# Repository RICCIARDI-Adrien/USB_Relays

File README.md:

# USB relays

Control separately 16 signal relays through a PC by using a standard USB connection and a simple text-based serial protocol.  
Each relay can switch up to 3A at 24VDC (warning : this board is not designed for AC current).  
There is no need for a separate power supply to power the board, it is designed to be fully powered by the USB connection (that's why small relays are used).

## Communication protocol

* The board provides an USB serial port with the following settings : **115200 bits/s, no parity, 1 stop bit**.
* All commands are ASCII-only to allow to easily use the board with a simple serial port terminal like `Putty`, `minicom`, `picocom`, etc. If you plan to send commands manually, enable local echo and send CRLF when pressing enter key (see below). Here is an example picocom command invocation : `picocom --echo --omap crcrlf -b 115200 /dev/ttyUSB0`.
* All commands start with the character `#`. This way, if you mess up and write the commands into an UNIX terminal, they will be interpreted as comments.
* All commands end with CRLF characters (`\r\n`), so you only have to press `enter` key to send the command to the board.
* All commands sent to the board return an answer, the board will ignore all other commands while it is processing the current one. This allows to throttle a fast PC sending too much commands at a time, it must wait for each command answer before sending the next one.
* If you don't know the board state (for instance, the PC rebooted while it was sending a command and the board has received an incomplete command and is stuck waiting for the remaining part of the command), send the `!` character at any time. The board will immediately clear its reception buffer.

## Commands list

Use the `#H<CR><LF>` command to display the following list of commands :
```
Commands :
  - Get a relay state : #Gxx
    'xx' is the relay ID, from 1 to 16.
  - Display this help : #H
  - Set led state : #Lv
    'v' is the led state value (0 to turn off, 1 to turn on, 2 to make it blink).
  - Set relay state : #Sxxv
    'xx' is the relay ID, from 1 to 16.
    'v' is the relay state value (0 to clear, 1 to set).
  - Get firmware version : #V
```

## Photo gallery

### Casing plates

Plates are made of 4mm-thick 304 stainless steel.

### PCB

PCB top :

PCB bottom :

### Assembled PCB

Assembled PCB top :

Assembled PCB bottom :

### Casing assembly

Screwing the bolts on the casing lower steel plate :

Fixing the PCB :

Fixing the casing upper steel plate :

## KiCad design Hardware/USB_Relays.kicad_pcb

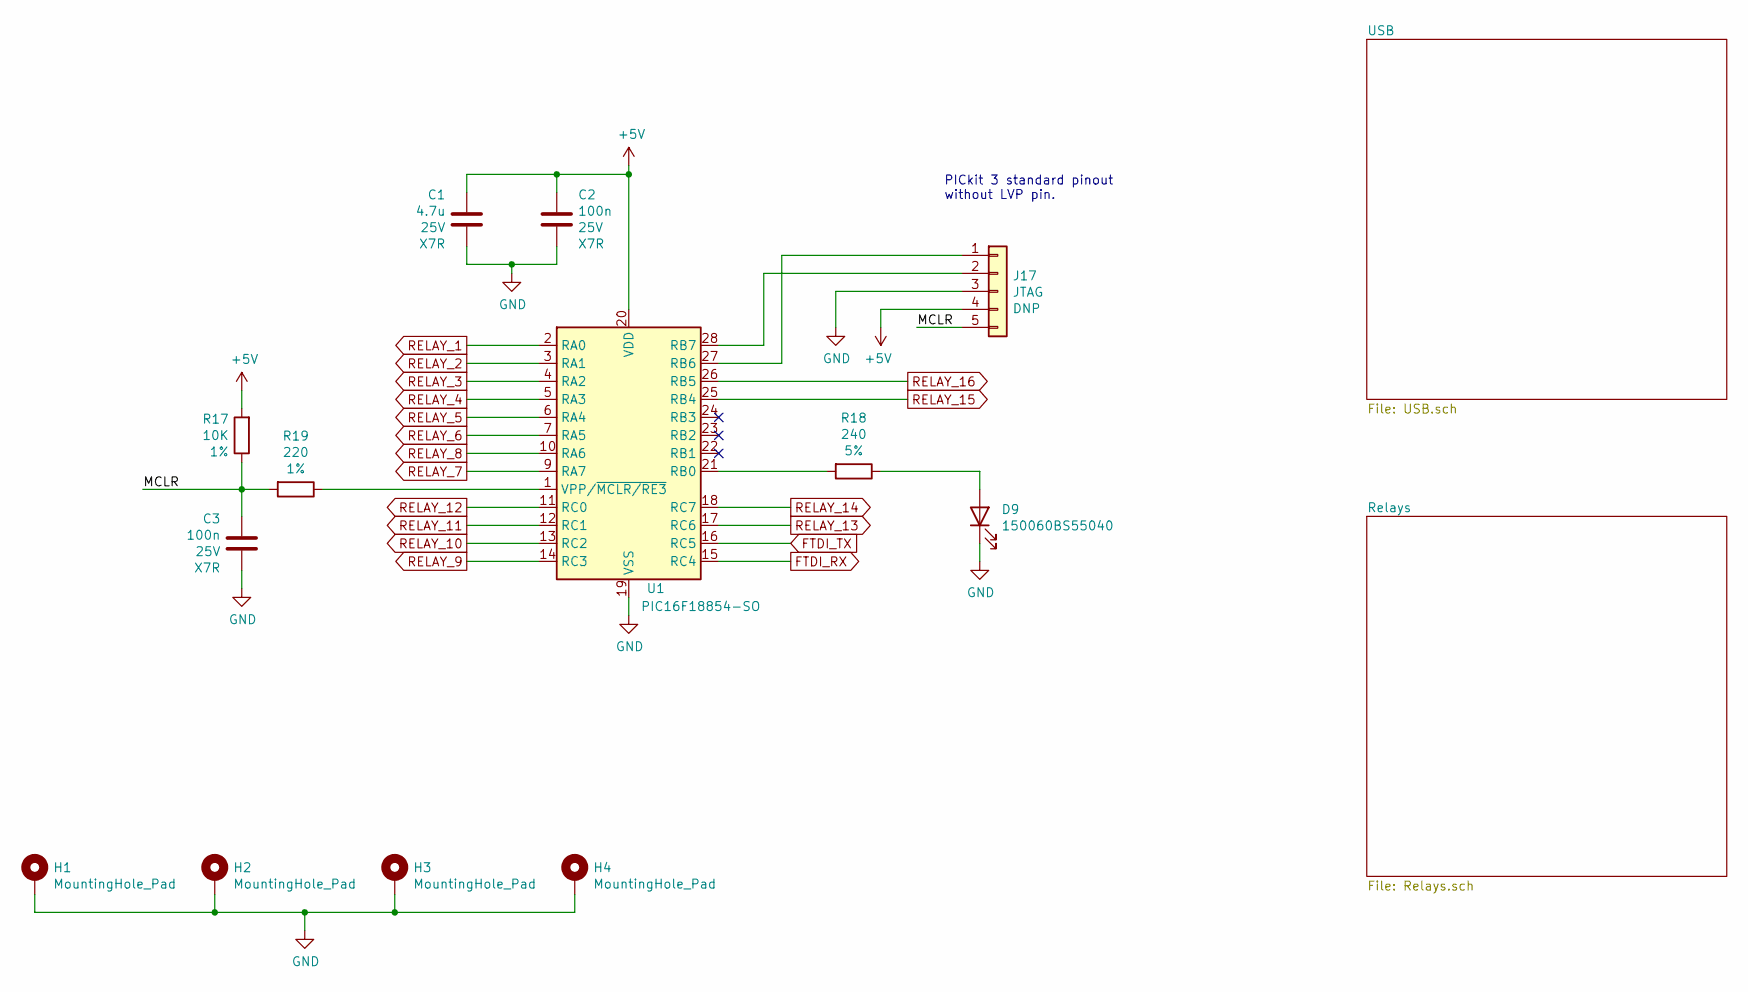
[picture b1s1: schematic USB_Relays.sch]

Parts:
C1: 4.7u; C_0805_2012Metric_Pad1.18x1.45mm_HandSolder
C2, C3: 100n; C_0603_1608Metric_Pad1.08x0.95mm_HandSolder
D9: 150060BS55040; LED_0603_1608Metric_Pad1.05x0.95mm_HandSolder
H1, H2, H3, H4: MountingHole_Pad; MountingHole_4.5mm_Pad
J17: JTAG; PinHeader_1x05_P2.54mm_Vertical
R17: 10K; R_0603_1608Metric_Pad0.98x0.95mm_HandSolder
R18: 240; R_1206_3216Metric_Pad1.30x1.75mm_HandSolder
R19: 220; R_0603_1608Metric_Pad0.98x0.95mm_HandSolder
U1: PIC16F18854-SO; SOIC-28W_7.5x17.9mm_P1.27mm

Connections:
+5V: C1.1, C2.1, J17.4, R17.2, U1.20 (VDD); also elsewhere on the board
/MCLR: C3.1, J17.5, R17.1, R19.2
FTDI_RX: U1.15 (RC4); also elsewhere on the board
FTDI_TX: U1.16 (RC5); also elsewhere on the board
GND: C1.2, C2.2, C3.2, D9.1 (K), H1.1, H2.1, H3.1, H4.1, J17.3, U1.8 (VSS), U1.19 (VSS); also elsewhere on the board
unnamed: D9.2 (A), R18.1
unnamed: J17.1, U1.27 (RB6)
unnamed: J17.2, U1.28 (RB7)
unnamed: R18.2, U1.21 (RB0)
unnamed: R19.1, U1.1 (VPP/~MCLR/RE3)
RELAY_1: U1.2 (RA0); also elsewhere on the board
RELAY_2: U1.3 (RA1); also elsewhere on the board
RELAY_3: U1.4 (RA2); also elsewhere on the board
RELAY_4: U1.5 (RA3); also elsewhere on the board
RELAY_5: U1.6 (RA4); also elsewhere on the board
RELAY_6: U1.7 (RA5); also elsewhere on the board
RELAY_7: U1.9 (RA7); also elsewhere on the board
RELAY_8: U1.10 (RA6); also elsewhere on the board
RELAY_9: U1.14 (RC3); also elsewhere on the board
RELAY_10: U1.13 (RC2); also elsewhere on the board
RELAY_11: U1.12 (RC1); also elsewhere on the board
RELAY_12: U1.11 (RC0); also elsewhere on the board
RELAY_13: U1.17 (RC6); also elsewhere on the board
RELAY_14: U1.18 (RC7); also elsewhere on the board
RELAY_15: U1.25 (RB4); also elsewhere on the board
RELAY_16: U1.26 (RB5); also elsewhere on the board

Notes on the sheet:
PICkit 3 standard pinout without LVP pin.

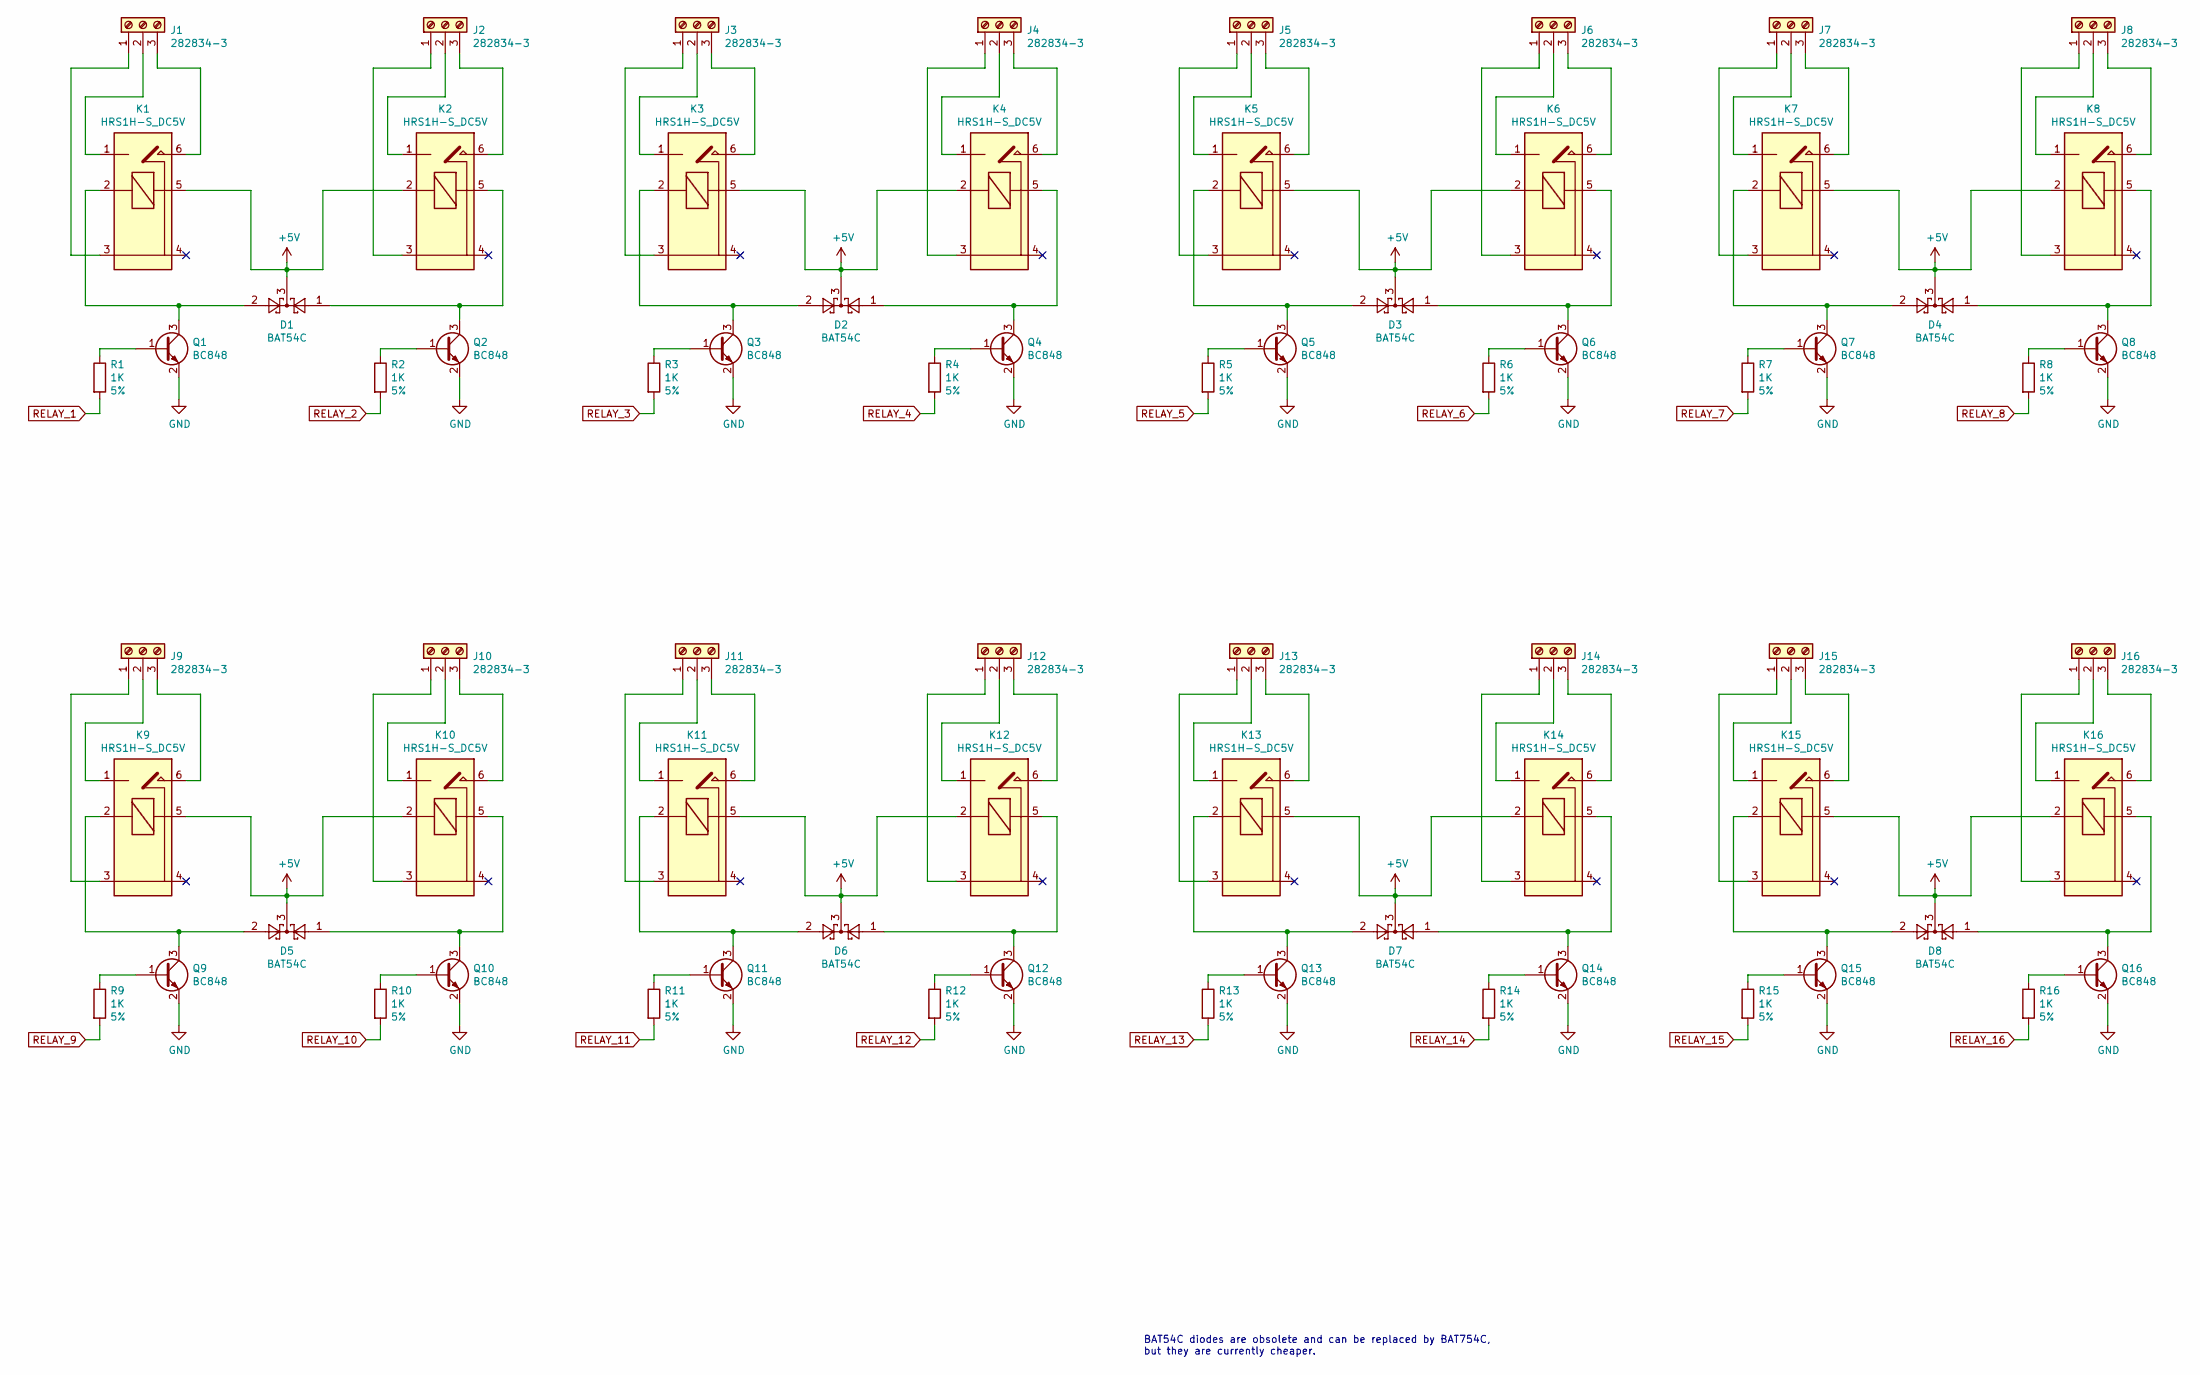
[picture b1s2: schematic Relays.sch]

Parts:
D1, D2, D3, D4, D5, D6, D7, D8: BAT54C; SOT-23
J1, J2, J3, J4, J5, J6, J7, J8, J9, J10, J11, J12, J13, J14, J15, J16: 282834-3; TerminalBlock_TE_282834-3_1x03_P2.54mm_Horizontal
K1, K2, K3, K4, K5, K6, K7, K8, K9, K10, K11, K12, K13, K14, K15, K16: HRS1H-S_DC5V; HRS1H-S
Q1, Q2, Q3, Q4, Q5, Q6, Q7, Q8, Q9, Q10, Q11, Q12, Q13, Q14, Q15, Q16: BC848; SOT-23
R1, R2, R3, R4, R5, R6, R7, R8, R9, R10, R11, R12, R13, R14, R15, R16: 1K; R_0603_1608Metric_Pad0.98x0.95mm_HandSolder

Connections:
+5V: D1.3, D2.3, D3.3, D4.3, D5.3, D6.3, D7.3, D8.3, K1.5, K2.2, K3.5, K4.2, K5.5, K6.2, K7.5, K8.2, K9.5, K10.2, K11.5, K12.2, K13.5, K14.2, K15.5, K16.2; also elsewhere on the board
GND: Q1.2 (E), Q2.2 (E), Q3.2 (E), Q4.2 (E), Q5.2 (E), Q6.2 (E), Q7.2 (E), Q8.2 (E), Q9.2 (E), Q10.2 (E), Q11.2 (E), Q12.2 (E), Q13.2 (E), Q14.2 (E), Q15.2 (E), Q16.2 (E); also elsewhere on the board
unnamed: D1.1, K2.5, Q2.3 (C)
unnamed: D1.2, K1.2, Q1.3 (C)
unnamed: D2.1, K4.5, Q4.3 (C)
unnamed: D2.2, K3.2, Q3.3 (C)
unnamed: D3.1, K6.5, Q6.3 (C)
unnamed: D3.2, K5.2, Q5.3 (C)
unnamed: D4.1, K8.5, Q8.3 (C)
unnamed: D4.2, K7.2, Q7.3 (C)
unnamed: D5.1, K10.5, Q10.3 (C)
unnamed: D5.2, K9.2, Q9.3 (C)
unnamed: D6.1, K12.5, Q12.3 (C)
unnamed: D6.2, K11.2, Q11.3 (C)
unnamed: D7.1, K14.5, Q14.3 (C)
unnamed: D7.2, K13.2, Q13.3 (C)
unnamed: D8.1, K16.5, Q16.3 (C)
unnamed: D8.2, K15.2, Q15.3 (C)
unnamed: J1.1, K1.3
unnamed: J1.2, K1.1
unnamed: J1.3, K1.6
unnamed: J2.1, K2.3
unnamed: J2.2, K2.1
unnamed: J2.3, K2.6
unnamed: J3.1, K3.3
unnamed: J3.2, K3.1
unnamed: J3.3, K3.6
unnamed: J4.1, K4.3
unnamed: J4.2, K4.1
unnamed: J4.3, K4.6
unnamed: J5.1, K5.3
unnamed: J5.2, K5.1
unnamed: J5.3, K5.6
unnamed: J6.1, K6.3
unnamed: J6.2, K6.1
unnamed: J6.3, K6.6
unnamed: J7.1, K7.3
unnamed: J7.2, K7.1
unnamed: J7.3, K7.6
unnamed: J8.1, K8.3
unnamed: J8.2, K8.1
unnamed: J8.3, K8.6
unnamed: J9.1, K9.3
unnamed: J9.2, K9.1
unnamed: J9.3, K9.6
unnamed: J10.1, K10.3
unnamed: J10.2, K10.1
unnamed: J10.3, K10.6
unnamed: J11.1, K11.3
unnamed: J11.2, K11.1
unnamed: J11.3, K11.6
unnamed: J12.1, K12.3
unnamed: J12.2, K12.1
unnamed: J12.3, K12.6
unnamed: J13.1, K13.3
unnamed: J13.2, K13.1
unnamed: J13.3, K13.6
unnamed: J14.1, K14.3
unnamed: J14.2, K14.1
unnamed: J14.3, K14.6
unnamed: J15.1, K15.3
unnamed: J15.2, K15.1
unnamed: J15.3, K15.6
unnamed: J16.1, K16.3
unnamed: J16.2, K16.1
unnamed: J16.3, K16.6
unnamed: Q1.1 (B), R1.1
unnamed: Q2.1 (B), R2.1
unnamed: Q3.1 (B), R3.1
unnamed: Q4.1 (B), R4.1
unnamed: Q5.1 (B), R5.1
unnamed: Q6.1 (B), R6.1
unnamed: Q7.1 (B), R7.1
unnamed: Q8.1 (B), R8.1
unnamed: Q9.1 (B), R9.1
unnamed: Q10.1 (B), R10.1
unnamed: Q11.1 (B), R11.1
unnamed: Q12.1 (B), R12.1
unnamed: Q13.1 (B), R13.1
unnamed: Q14.1 (B), R14.1
unnamed: Q15.1 (B), R15.1
unnamed: Q16.1 (B), R16.1
RELAY_1: R1.2; also elsewhere on the board
RELAY_2: R2.2; also elsewhere on the board
RELAY_3: R3.2; also elsewhere on the board
RELAY_4: R4.2; also elsewhere on the board
RELAY_5: R5.2; also elsewhere on the board
RELAY_6: R6.2; also elsewhere on the board
RELAY_7: R7.2; also elsewhere on the board
RELAY_8: R8.2; also elsewhere on the board
RELAY_9: R9.2; also elsewhere on the board
RELAY_10: R10.2; also elsewhere on the board
RELAY_11: R11.2; also elsewhere on the board
RELAY_12: R12.2; also elsewhere on the board
RELAY_13: R13.2; also elsewhere on the board
RELAY_14: R14.2; also elsewhere on the board
RELAY_15: R15.2; also elsewhere on the board
RELAY_16: R16.2; also elsewhere on the board

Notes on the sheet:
BAT54C diodes are obsolete and can be replaced by BAT754C, but they are currently cheaper.

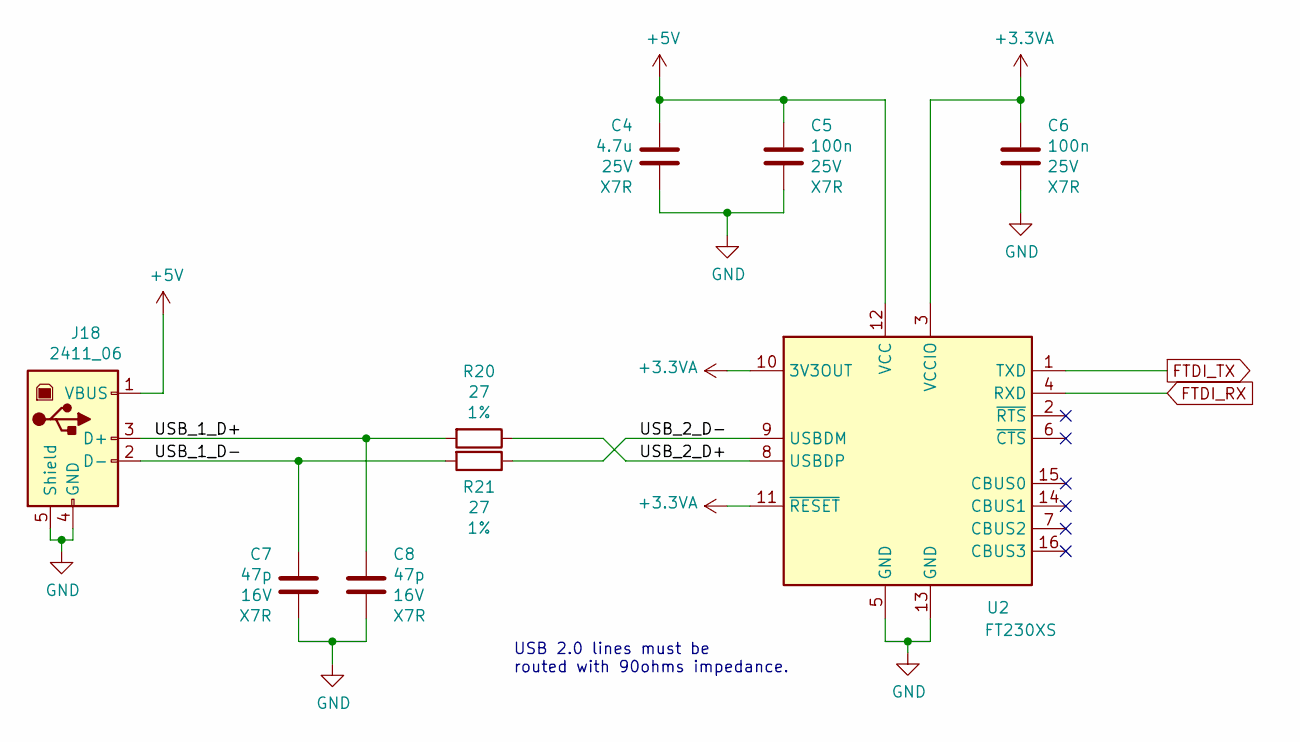
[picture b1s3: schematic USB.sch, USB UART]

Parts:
C4: 4.7u; C_0805_2012Metric_Pad1.18x1.45mm_HandSolder
C5, C6: 100n; C_0603_1608Metric_Pad1.08x0.95mm_HandSolder
C7, C8: 47p; C_0603_1608Metric_Pad1.08x0.95mm_HandSolder
J18: 2411_06; USB_B_OST_USB-B1HSxx_Horizontal
R20, R21: 27; R_0603_1608Metric_Pad0.98x0.95mm_HandSolder
U2: FT230XS; SSOP-16_3.9x4.9mm_P0.635mm

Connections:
+3.3VA: C6.1, U2.3 (VCCIO), U2.10 (3V3OUT), U2.11 (~RESET)
+5V: C4.1, C5.1, J18.1 (VBUS), U2.12 (VCC); also elsewhere on the board
/USB/USB_1_D+: C8.1, J18.3 (D+), R20.2
/USB/USB_1_D-: C7.1, J18.2 (D-), R21.2
/USB/USB_2_D+: R20.1, U2.8 (USBDP)
/USB/USB_2_D-: R21.1, U2.9 (USBDM)
FTDI_RX: U2.4 (RXD); also elsewhere on the board
FTDI_TX: U2.1 (TXD); also elsewhere on the board
GND: C4.2, C5.2, C6.2, C7.2, C8.2, J18.4 (GND), J18.5 (Shield), U2.5 (GND), U2.13 (GND); also elsewhere on the board

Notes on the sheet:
USB 2.0 lines must be routed with 90ohms impedance.

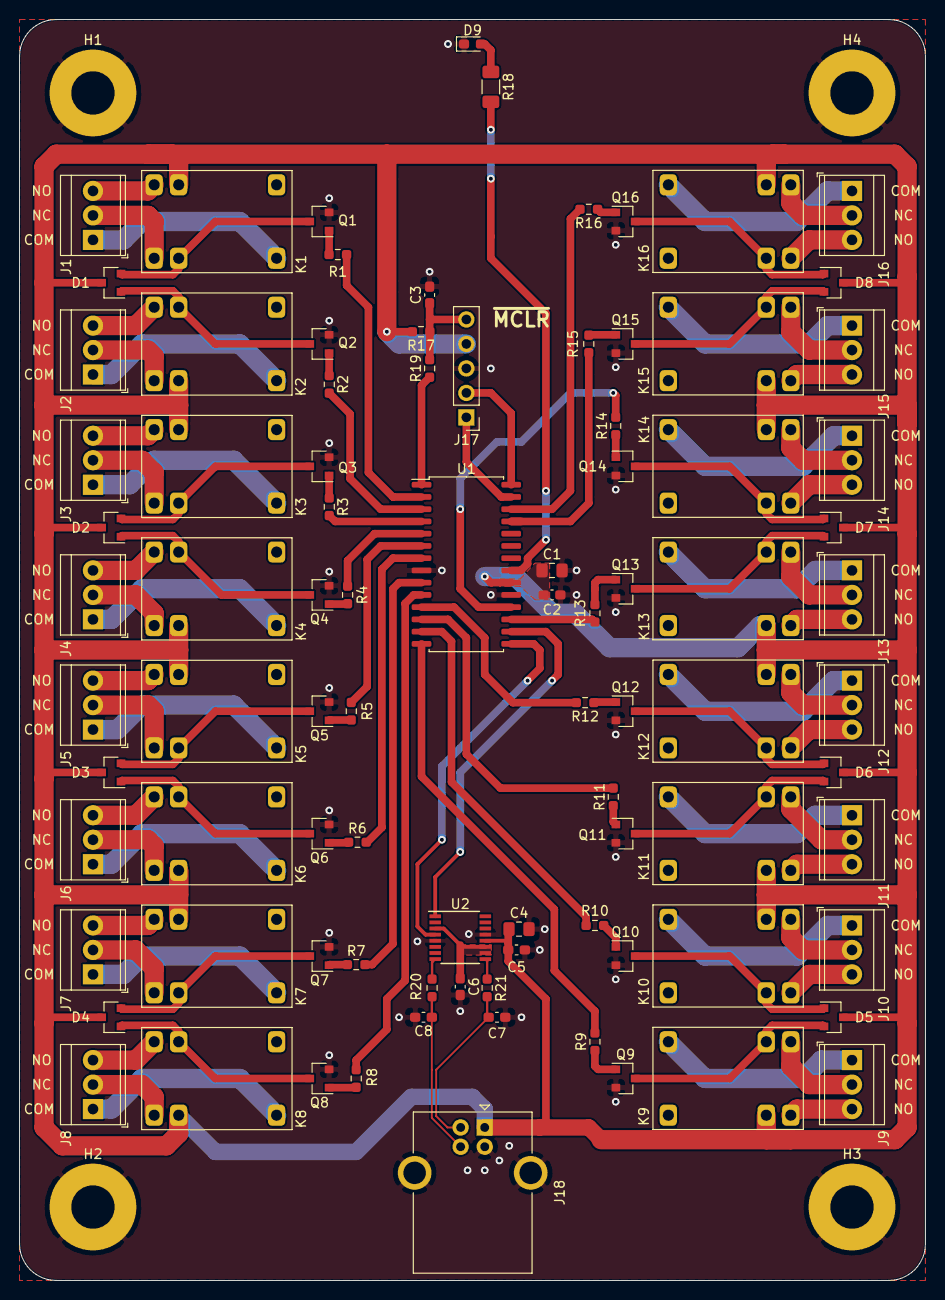
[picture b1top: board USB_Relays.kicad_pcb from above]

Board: 2 copper layers, 94.0 x 130.8 mm, 94 parts (0 on the bottom side), 111 nets.

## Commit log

2021-08-12 Initial commit. Added README.md.
2021-08-12 [Hardware] Started schematic. Added USB UART sheet.
2021-08-12 [Hardware] Added USB-B connector reference and 3D model.
2021-08-12 [Hardware] Added HRS1H-S DC5V relay symbol, footprint and 3D model.
2021-08-12 [Hardware] Added relays schematic sheet.
2021-08-12 [Hardware] Added terminal 3D models.
2021-08-13 [Hardware] Added microcontroller-related schematic.
2021-08-13 [Hardware] Positioned components on PCB.
2021-08-13 [Hardware] Renamed components in a more coherent way.
2021-08-14 [Hardware] Ignored KiCad automatically generated cache file.
2021-08-14 [Hardware] Added mounting holes, PCB contour and ground planes.
2021-08-14 [Hardware] Routed whole PCB.
2021-08-14 [Hardware] Moved LED to make it more visible, cleaned components designation positions, added information about connectors pins to the PCB.
2021-08-14 [Hardware] Made round PCB corners.
2021-08-14 [Casing] Added first casing version with top and bottom plates, plus top plate holes to get access to terminal blocks.
2021-08-14 [Hardware] Improved bill of materials generation.
2021-08-15 Added MIT license and more description to README.md.
2021-08-30 [Firmware] Added empty project with blinking led test.
2021-08-31 [Firmware] Added relay module and a simple test.
2021-08-31 [Firmware] Added UART module and a simple test.
2021-08-31 [Firmware] Moved led management code to a dedicated module.
2021-09-01 [Firmware] Started communication protocol implementation. Added the 'get version' command.
2021-09-01 [Firmware] Added 'set relay state' communication protocol command.
2021-09-01 [Firmware] Added 'get relay state' communication protocol command.
2021-09-01 [Firmware] Added 'clear relay state' communication protocol command.
2021-09-01 [Firmware] Added 'set led state' communication protocol command.
2021-09-02 [Firmware] Removed 'clear relay state' communication protocol command and allowed to set or clear a relay from the 'set relay state' command. This is the same philosophy than the 'set led' command.
2021-09-02 [Firmware] Added 'help' communication protocol command.
2021-09-02 [Firmware] Allowed to make the led blink through the 'set led state' communication protocol command. This is useful to find a specific board in the middle of a lab.
2021-09-02 Added communication protocol and commands information to README.md.
2021-09-02 [Hardware] Inverted relays 'NC' and 'NO' markings on PC silkscreen to match real relay internal connections.
2021-09-02 [Software] Added a simple Linux shell script testing some of the board features.
2021-09-04 [Resources] Added most important parts datasheets.
2021-09-04 [Software] Added more tests to the board testing script.
2021-09-04 [Resources] Added casing plates and PCB pictures to README.md photo gallery.
2022-12-20 Added all required pictures to README.md.
2022-12-20 [Firmware] Increased UART baud rate from 9600 bit/s to 115200 bit/s.
2022-12-20 [Firmware] Bumped version to 1.1.
2022-12-20 [Software] Increased the board testing script serial port speed to 115200 bit/s.
2022-12-21 Updated serial port baud rate in README.md.
